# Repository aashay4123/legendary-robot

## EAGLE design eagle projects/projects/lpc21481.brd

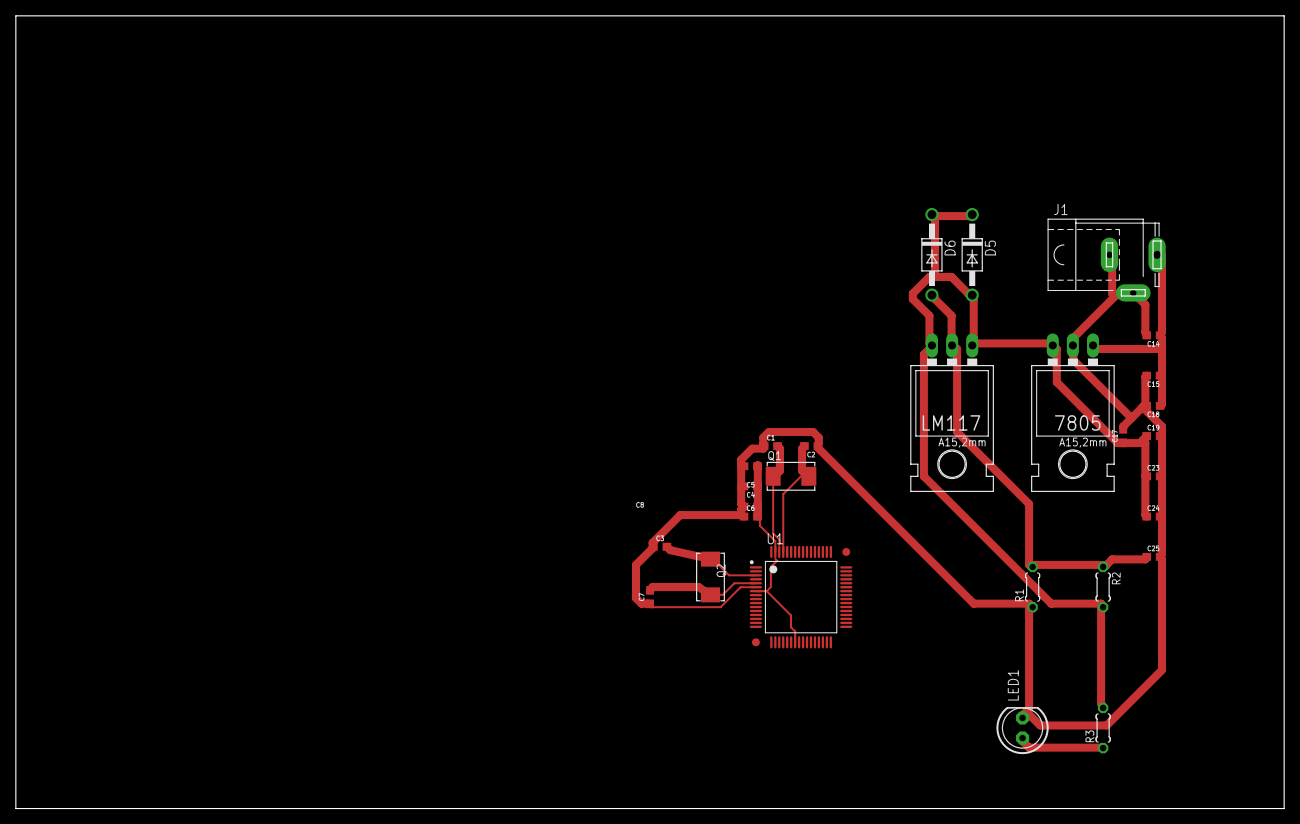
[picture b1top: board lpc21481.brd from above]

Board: 2 copper layers, 160.0 x 100.0 mm, 28 parts (0 on the bottom side), 12 nets.

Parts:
7805: 78XXL
C1, C2, C3, C4, C5, C6, C7, C8: 0.1uF; 0603
C14: 470UF; 0603
C15: 0.1UF; 0603
C17, C19: 10uF; 0603
C18: 22pF; 0603
C23: 0.1Uf; 0603
C24: 220uF; 0603
C25: 10uf; 0603
D5, D6: 1N4004; DO41-10
J1: SPC4078
LED1: LED5MM
LM117: 78XXL
Q1, Q2: 6.0X3.5_2
R1: 392; 0204/5
R2: 240; 0204/5
R3: 150; 0204/5
U1: LPC2148FBD64; TSQFP50P1200X1200X160-64N

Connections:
3.3V: C4.1, C5.1, C6.2, C8.1, U1.63
5V: 7805.OUT, C17.1, C19.1, C23.1, C24.1, D5.A, D5.C, D6.C, LM117.IN, LM117.OUT, R2.2, R3.2
12V: 7805.IN, C14.1, C15.1, C18.1, J1.3
GND: 7805.GND, C1.1, C2.1, C3.1, C4.2, C5.2, C6.1, C7.1, C8.2, C14.2, C15.2, C17.2, C18.2, C19.2, C23.2, C24.2, C25.2, J1.1, J1.2, LED1.K, R1.1, U1.6, U1.18, U1.25, U1.42, U1.50, U1.59
unnamed: C1.2, Q1.1, U1.62
unnamed: C2.2, Q1.2, U1.61
unnamed: C3.2, Q2.1, U1.3
unnamed: C7.2, Q2.2, U1.5
unnamed: C25.1, D6.A, LM117.GND, R1.2, R2.1
unnamed: LED1.A, R3.1
S$1: U1.7, U1.23
S$2: U1.43, U1.49, U1.51

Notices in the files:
parts and their libraries:
SparkFun-Capacitors: Licensing: Creative Commons ShareAlike 4.0 International - https://creativecommons.org/licenses/by-sa/4.0
crystal-geyer_V1_0: Copyright: Geyer-Electronic
philips-5: Copyright 2006 Weartronics
